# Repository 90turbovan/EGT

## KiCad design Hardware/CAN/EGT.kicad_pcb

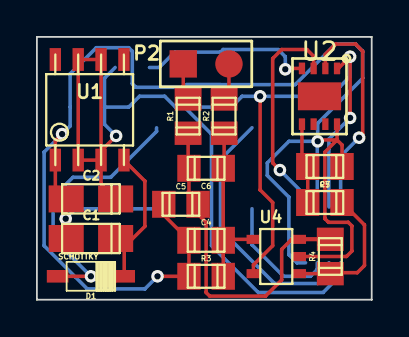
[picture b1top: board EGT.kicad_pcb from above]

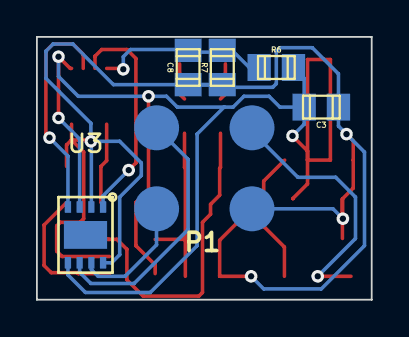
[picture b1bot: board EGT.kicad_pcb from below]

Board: 2 copper layers, 18.6 x 14.6 mm, 22 parts (6 on the bottom side), 15 nets.

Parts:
C1, C2: 10uF; c_tant_A
C3: 100nF; c_0805
C4, C5, C6, C7, C8: C; c_0805
D1: SCHOTTKY; SOD-123
P1: CONN_4; EGT_connector
P2: CONN_2; EGT_thermo
R1, R2, R3, R4, R5, R6, R7: R; c_0805
U1: MC33269; so-8
U2: PIC12F1840; dfn8
U3: TJA1051TK/3; dfn8
U4: AD8628; SOT23-5

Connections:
unnamed: U2.2, U3.4
unnamed: C7.1, R5.2, U2.5
unnamed: U2.3, U3.1
unnamed: C1.1, D1.2, U1.4
unnamed: C8.1, R6.2, R7.1, U2.4
unnamed: C2.1, C3.1, R6.1, U1.2, U1.3, U1.6, U1.7, U2.1, U3.3, U3.5, U4.5
unnamed: D1.1, P1.1
unnamed: C1.2, C2.2, C3.2, C4.2, C5.2, C7.2, C8.2, P1.2, R3.2, R7.2, U1.1, U2.8, U3.2, U3.8, U4.2
unnamed: P1.4, U3.7
unnamed: P1.3, U3.6
unnamed: C5.1, C6.1, R1.2, R4.1, U4.3
unnamed: P2.2, R2.1
unnamed: C4.1, C6.2, R2.2, R3.1, U4.4
unnamed: R4.2, R5.1, U4.1
unnamed: P2.1, R1.1

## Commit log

2013-06-24 File structure reorganization
2013-06-24 Added components, library
2013-07-02 Schematic work
2013-07-03 Preliminary schematic, test board layout
2013-07-03 Final routing
2013-07-09 Revised Op Amp choice, added analog and digital output. Added ISCP Connector
